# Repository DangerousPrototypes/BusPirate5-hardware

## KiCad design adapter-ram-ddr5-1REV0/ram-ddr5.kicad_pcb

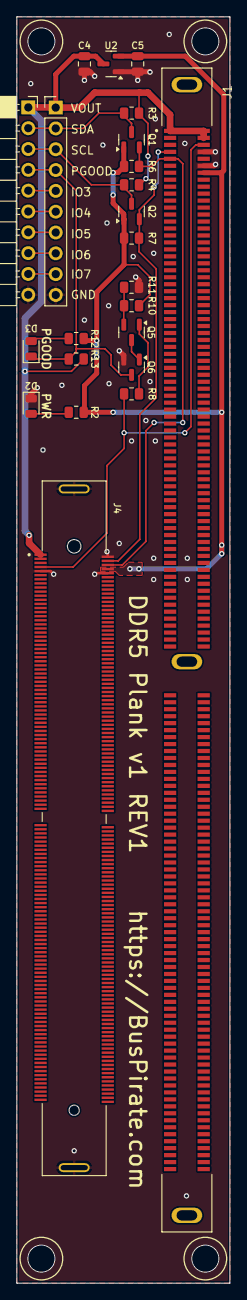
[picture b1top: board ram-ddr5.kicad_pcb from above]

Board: 2 copper layers, 26.0 x 154.5 mm, 23 parts (0 on the bottom side), 19 nets.

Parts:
C4, C5: 10uF/6.3V; C_0805_2012Metric
D2, D3: LED; LED_0805_2012Metric
J1: DDR504111002KQ; DDR5 UDIMM GENERIC
J2: Conn_01x10; PinSocket_1x10_P2.54mm_Horizontal
J3: Conn_01x10; PinHeader_1x10_P2.54mm_Vertical
J4: 10160554-001SHLF; AMPHENOL_10160554-001SHLF
Q1, Q2: 2N7002; SOT-23
Q5: BC807; SOT-23
Q6: BC817; SOT-23
R2, R12, R13: 6.8K; R_0805_2012Metric
R3, R4, R6, R7: 2K; R_0805_2012Metric
R8: 1K; R_0805_2012Metric
R10: 680R; R_0805_2012Metric
R11: 330R; R_0805_2012Metric
U2: MCP1700x-330xxTT; SOT-23

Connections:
+3.3V: C5.1, J1.151, J4.8, Q1.1 (G), Q2.1 (G), R2.1, R6.2, R7.2, R10.2, R12.1, U2.2 (VO)
BULK_VIN: C4.1, J1.01, J1.145, J1.146, J2.1, J3.1, J4.1, J4.3, R3.2, R4.2, R13.2, U2.3 (VI)
GND: C4.2, C5.2, D2.1 (K), J1.148, J1.150, J2.10, J3.10, J4.2, J4.9, J4.10, J4.SH, Q6.2 (E), R11.1, U2.1 (GND)
HSCL: J1.04, J4.4, Q2.2 (S), R7.1
HSDA: J1.05, J4.6, Q1.2 (S), R6.1
unnamed: D2.2 (A), R2.2
unnamed: D3.2 (A), R12.2
unnamed: J2.5, J3.5
unnamed: J2.6, J3.6
unnamed: J2.7, J3.7
unnamed: J2.8, J3.8
unnamed: J2.9, J3.9
unnamed: Q5.1 (B), R8.2
unnamed: Q5.3 (C), Q6.1 (B)
unnamed: Q5.2 (E), R10.1, R11.2
PWR_GOOD: J1.147, J4.7, R8.1
PWR_GOOD_OUT: D3.1 (K), J2.4, J3.4, Q6.3 (C), R13.1
SCL: J2.3, J3.3, Q2.3 (D), R4.1
SDA: J2.2, J3.2, Q1.3 (D), R3.1

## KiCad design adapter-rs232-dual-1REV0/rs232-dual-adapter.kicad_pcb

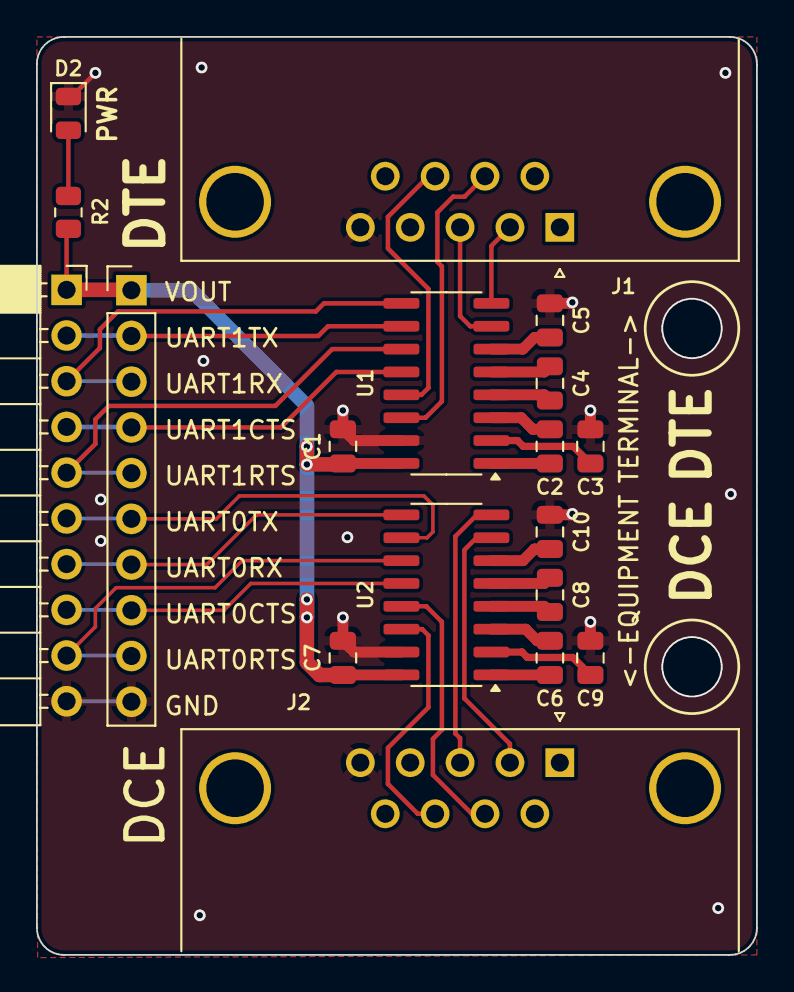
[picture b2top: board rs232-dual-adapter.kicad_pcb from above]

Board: 2 copper layers, 40.0 x 51.0 mm, 18 parts (0 on the bottom side), 31 nets.

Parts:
C1, C2, C6, C7: 0.1uF; C_0805_2012Metric
C3, C4, C5, C8, C9, C10: 0.47uF; C_0805_2012Metric
D2: LED; LED_0805_2012Metric
J1: COM1; DSUB-9_Male_Horizontal_P2.77x2.84mm_EdgePinOffset7.70mm_Hou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
J2: COM2; DSUB-9_Female_Horizontal_P2.77x2.84mm_EdgePinOffset7.70mm_H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
J3: Conn_01x10; PinHeader_1x10_P2.54mm_Vertical
J4: Conn_01x10; PinSocket_1x10_P2.54mm_Horizontal
R2: 2K; R_0805_2012Metric
U1, U2: MAX3232; SOP-16_3.9x9.9mm_P1.27mm

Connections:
/DCE_CTS: J2.8, U2.14 (T1OUT)
/DCE_RTS: J2.7, U2.13 (R1IN)
/DCE_RXD: J2.2, U2.7 (T2OUT)
/DCE_TXD: J2.3, U2.8 (R2IN)
/DTE_CTS: J1.8, U1.13 (R1IN)
/DTE_RTS: J1.7, U1.14 (T1OUT)
/DTE_RXD: J1.2, U1.8 (R2IN)
/DTE_TXD: J1.3, U1.7 (T2OUT)
GND: C1.2, C3.2, C5.2, C7.2, C9.2, C10.2, D2.1 (K), J1.5, J2.5, J3.10, J4.10, U1.15 (GND), U2.15 (GND)
unnamed: D2.2 (A), R2.2
unnamed: C2.1, U1.1 (C1+)
unnamed: C2.2, U1.3 (C1-)
unnamed: C4.1, U1.4 (C2+)
unnamed: C4.2, U1.5 (C2-)
unnamed: C3.1, U1.2 (VS+)
unnamed: C5.1, U1.6 (VS-)
unnamed: C6.1, U2.1 (C1+)
unnamed: C6.2, U2.3 (C1-)
unnamed: C8.1, U2.4 (C2+)
unnamed: C8.2, U2.5 (C2-)
unnamed: C9.1, U2.2 (VS+)
unnamed: C10.1, U2.6 (VS-)
UART0CTS: J3.8, J4.8, U2.12 (R1OUT)
UART0RTS: J3.9, J4.9, U2.11 (T1IN)
UART0RX: J3.7, J4.7, U2.9 (R2OUT)
UART0TX: J3.6, J4.6, U2.10 (T2IN)
UART1CTS: J3.4, J4.4, U1.12 (R1OUT)
UART1RTS: J3.5, J4.5, U1.11 (T1IN)
UART1RX: J3.3, J4.3, U1.9 (R2OUT)
UART1TX: J3.2, J4.2, U1.10 (T2IN)
VOUT: C1.1, C7.1, J3.1, J4.1, R2.1, U1.16 (VCC), U2.16 (VCC)

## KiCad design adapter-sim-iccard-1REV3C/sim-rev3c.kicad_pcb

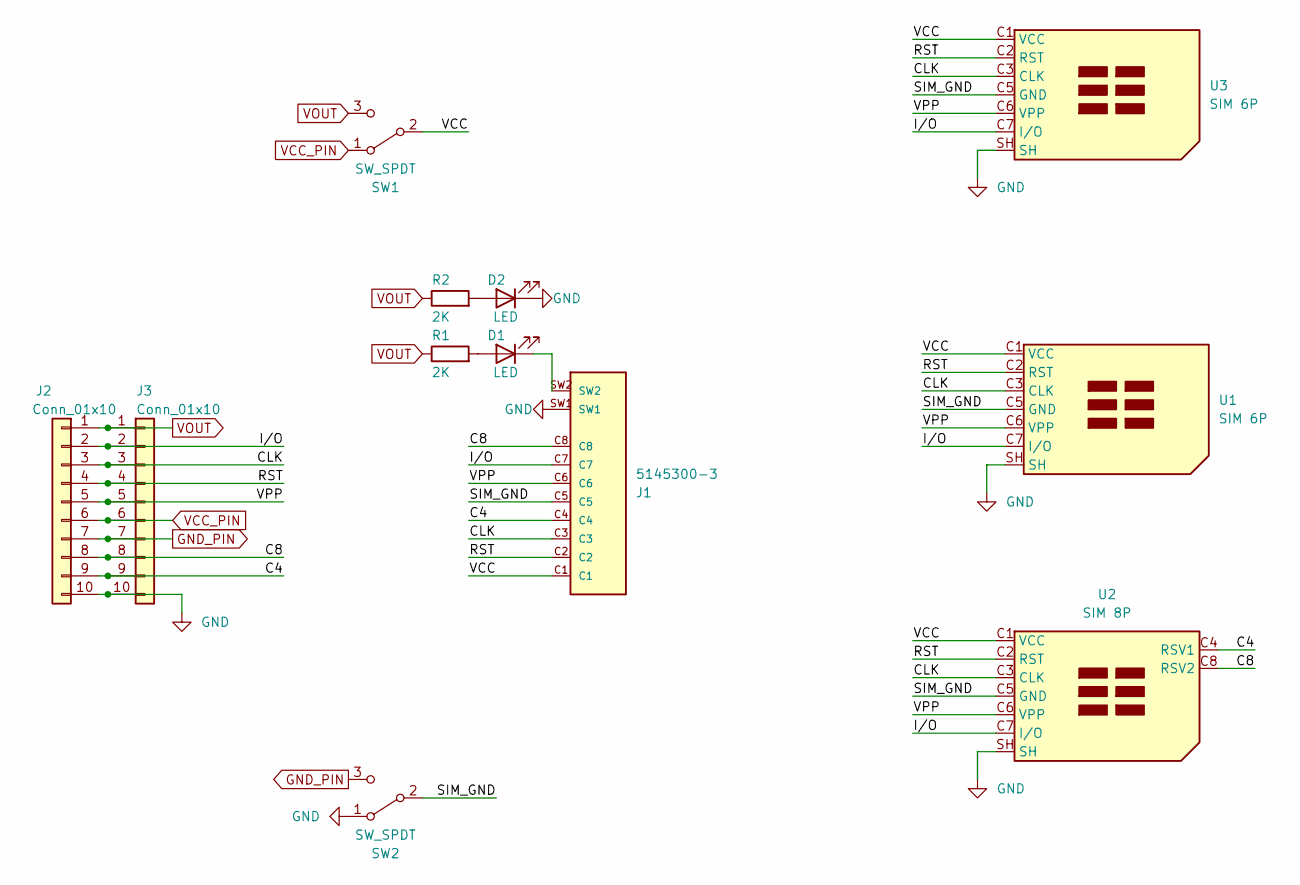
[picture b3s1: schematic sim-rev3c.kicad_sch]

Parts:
D1, D2: LED; LED_0805_2012Metric
J1: 5145300-3; TE_5145300-3; PARTREV C3
J2: Conn_01x10; PinSocket_1x10_P2.54mm_Horizontal
J3: Conn_01x10; PinHeader_1x10_P2.54mm_Vertical
R1, R2: 2K; R_0805_2012Metric
SW1, SW2: SW_SPDT; SW_SPDT_PCM12
U1: SIM 6P; DGLZ-SIM-0004
U2: SIM 8P; SIM-0030
U3: SIM 6P; SIM-0036

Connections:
/C4: J1.C4, J2.9, J3.9, U2.C4 (RSV1)
/C8: J1.C8, J2.8, J3.8, U2.C8 (RSV2)
/CLK: J1.C3, J2.3, J3.3, U1.C3 (CLK), U2.C3 (CLK), U3.C3 (CLK)
/I/O: J1.C7, J2.2, J3.2, U1.C7 (I/O), U2.C7 (I/O), U3.C7 (I/O)
/RST: J1.C2, J2.4, J3.4, U1.C2 (RST), U2.C2 (RST), U3.C2 (RST)
/SIM_GND: J1.C5, SW2.2 (B), U1.C5 (GND), U2.C5 (GND), U3.C5 (GND)
/VCC: J1.C1, SW1.2 (B), U1.C1 (VCC), U2.C1 (VCC), U3.C1 (VCC)
/VPP: J1.C6, J2.5, J3.5, U1.C6 (VPP), U2.C6 (VPP), U3.C6 (VPP)
GND: D2.1 (K), J1.SW1, J2.10, J3.10, SW2.1 (A), U1.SH, U2.SH, U3.SH
GND_PIN: J2.7, J3.7, SW2.3 (C)
unnamed: D1.2 (A), R1.2
unnamed: D1.1 (K), J1.SW2
unnamed: D2.2 (A), R2.2
VCC_PIN: J2.6, J3.6, SW1.1 (A)
VOUT: J2.1, J3.1, R1.1, R2.1, SW1.3 (C)

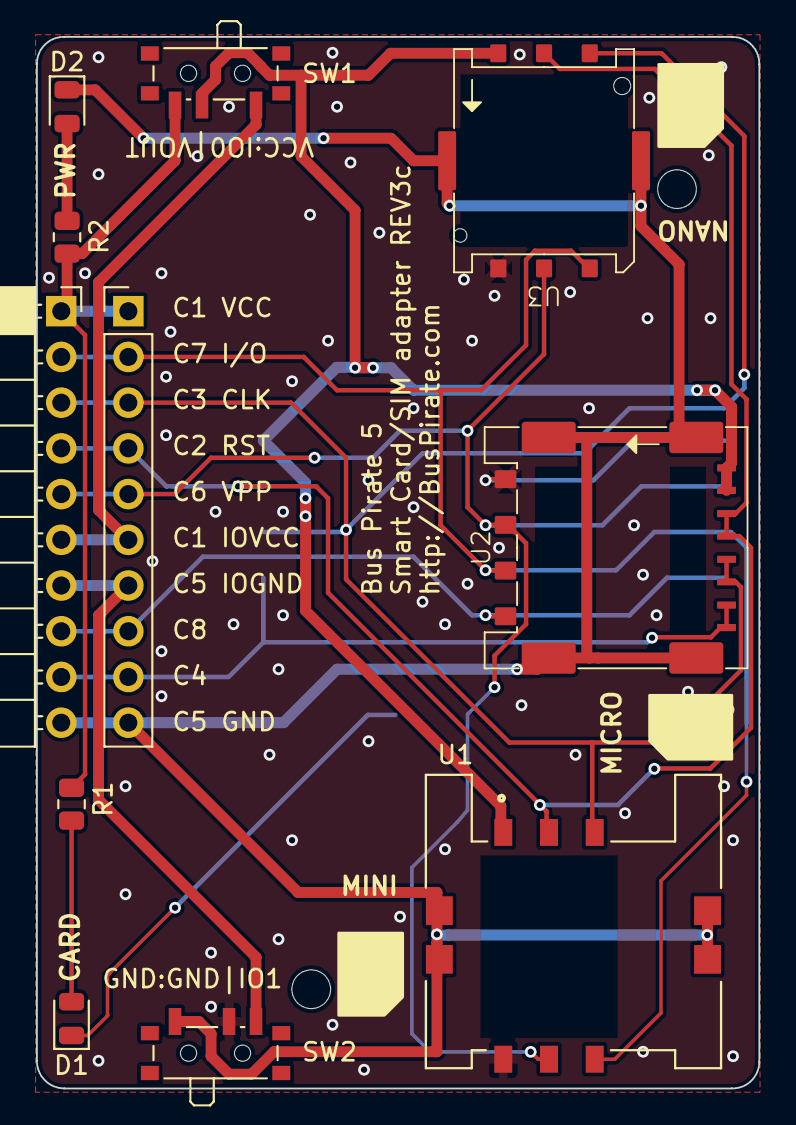
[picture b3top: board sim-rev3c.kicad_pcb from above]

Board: 2 copper layers, 40.1 x 58.4 mm, 12 parts (1 on the bottom side), 15 nets.

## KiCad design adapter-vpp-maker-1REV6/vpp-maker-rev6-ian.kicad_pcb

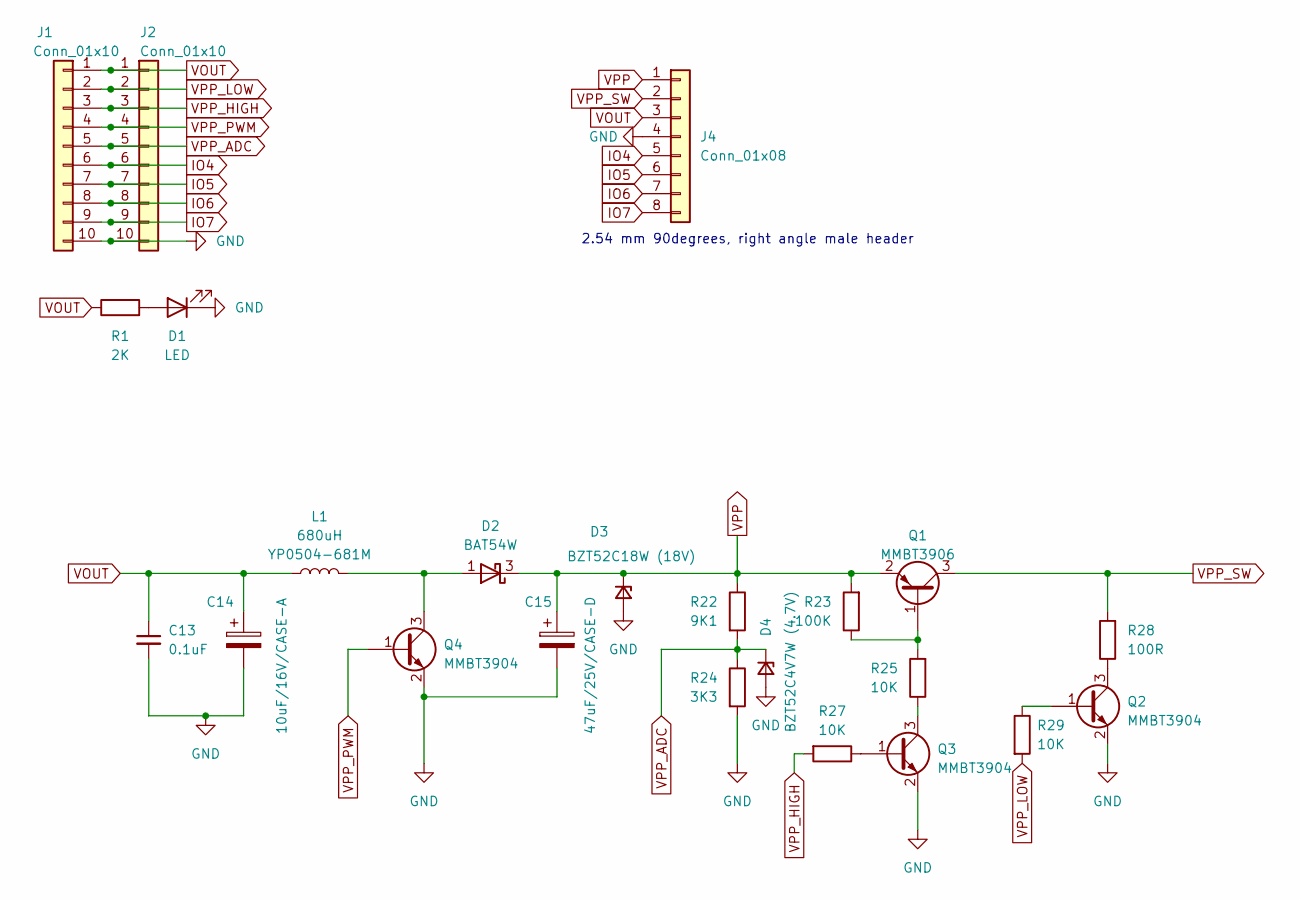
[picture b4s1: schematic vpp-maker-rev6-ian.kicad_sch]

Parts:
C13: 0.1uF; C_0805_2012Metric_Pad1.18x1.45mm_HandSolder
C14: 10uF/16V/CASE-A; CP_EIA-3216-18_Kemet-A
C15: 47uF/25V/CASE-D; CP_EIA-7343-31_Kemet-D
D1: LED; LED_0805_2012Metric
D2: BAT54W; SOT-23
D3: BZT52C18W (18V); D_SOD-123
D4: BZT52C4V7W (4.7V); D_SOD-123
J1: Conn_01x10; PinSocket_1x10_P2.54mm_Horizontal
J2: Conn_01x10; PinHeader_1x10_P2.54mm_Vertical
J4: Conn_01x08; PinHeader_1x08_P2.54mm_Horizontal
L1: 680uH; L_YP0504; MPN YP0504-681M
Q1: MMBT3906; SOT-23
Q2, Q3, Q4: MMBT3904; SOT-23
R1: 2K; R_0805_2012Metric
R22: 9K1; R_0805_2012Metric
R23: 100K; R_0805_2012Metric
R24: 3K3; R_0805_2012Metric
R25, R27, R29: 10K; R_0805_2012Metric
R28: 100R; R_0805_2012Metric

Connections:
GND: C13.2, C14.2, C15.2, D1.1 (K), D3.2 (A), D4.2 (A), J1.10, J2.10, J4.4, Q2.2 (E), Q3.2 (E), Q4.2 (E), R24.2
IO4: J1.6, J2.6, J4.5
IO5: J1.7, J2.7, J4.6
IO6: J1.8, J2.8, J4.7
IO7: J1.9, J2.9, J4.8
unnamed: D1.2 (A), R1.2
unnamed: D2.1 (A), L1.2, Q4.3 (C)
unnamed: Q1.1 (B), R23.1, R25.2
unnamed: Q2.1 (B), R29.1
unnamed: Q2.3 (C), R28.1
unnamed: Q3.1 (B), R27.1
unnamed: Q3.3 (C), R25.1
VOUT: C13.1, C14.1, J1.1, J2.1, J4.3, L1.1, R1.1
VPP: C15.1, D2.3 (K), D3.1 (K), J4.1, Q1.2 (E), R22.1, R23.2
VPP_ADC: D4.1 (K), J1.5, J2.5, R22.2, R24.1
VPP_HIGH: J1.3, J2.3, R27.2
VPP_LOW: J1.2, J2.2, R29.2
VPP_PWM: J1.4, J2.4, Q4.1 (B)
VPP_SW: J4.2, Q1.3 (C), R28.2

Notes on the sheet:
2.54 mm 90degrees, right angle male header

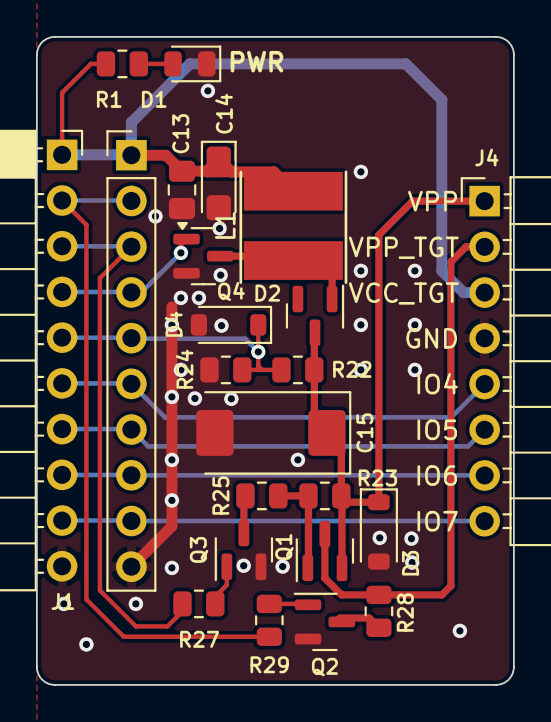
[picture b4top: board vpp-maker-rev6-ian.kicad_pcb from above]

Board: 2 copper layers, 26.5 x 36.0 mm, 23 parts (0 on the bottom side), 19 nets.

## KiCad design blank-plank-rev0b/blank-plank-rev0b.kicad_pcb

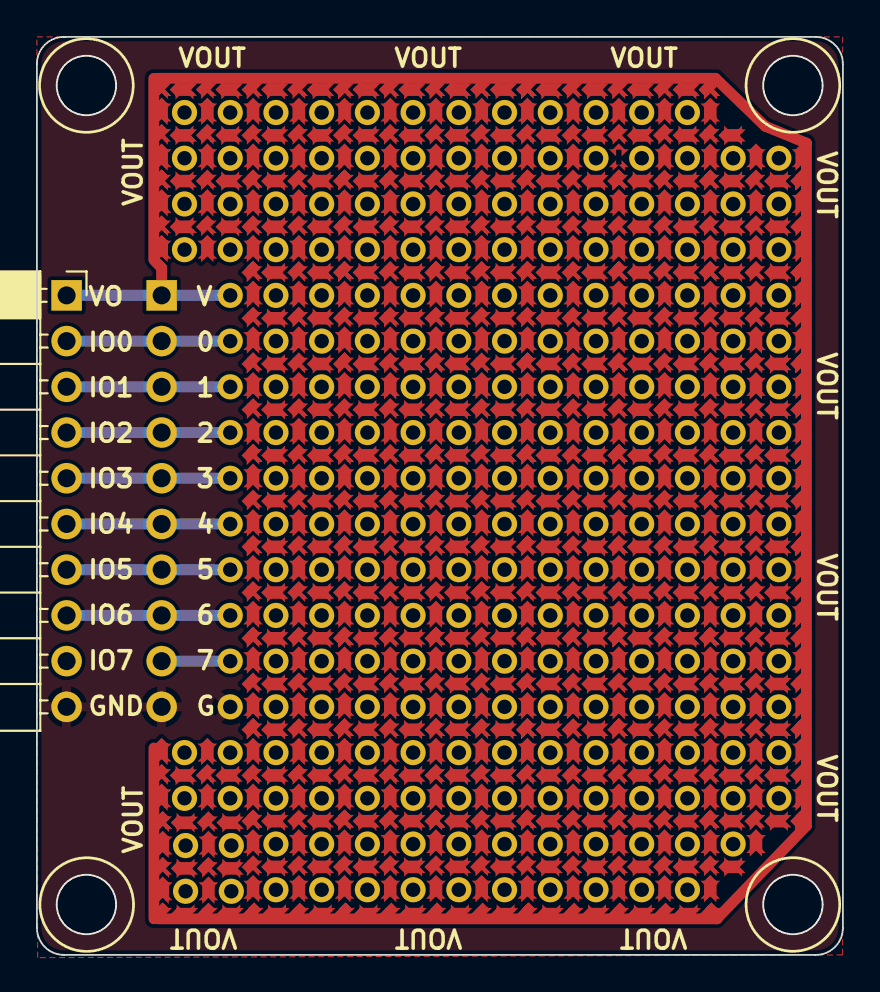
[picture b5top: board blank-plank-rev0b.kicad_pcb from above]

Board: 2 copper layers, 44.8 x 51.0 mm, 3 parts (0 on the bottom side), 10 nets.

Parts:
J2: Conn_01x10; PinSocket_1x10_P2.54mm_Horizontal
J3: Conn_01x10; PinHeader_1x10_P2.54mm_Vertical_No_Silk
J5: Conn_01x10; PinHeader_1x10_P2.54mm_Vertical_Reduced_2

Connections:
GND: J2.10, J3.10, J5.10
IO0: J2.2, J3.2, J5.2
IO1: J2.3, J3.3, J5.3
IO2: J2.4, J3.4, J5.4
IO3: J2.5, J3.5, J5.5
IO4: J2.6, J3.6, J5.6
IO5: J2.7, J3.7, J5.7
IO6: J2.8, J3.8, J5.8
IO7: J2.9, J3.9, J5.9
VOUT: J2.1, J3.1, J5.1

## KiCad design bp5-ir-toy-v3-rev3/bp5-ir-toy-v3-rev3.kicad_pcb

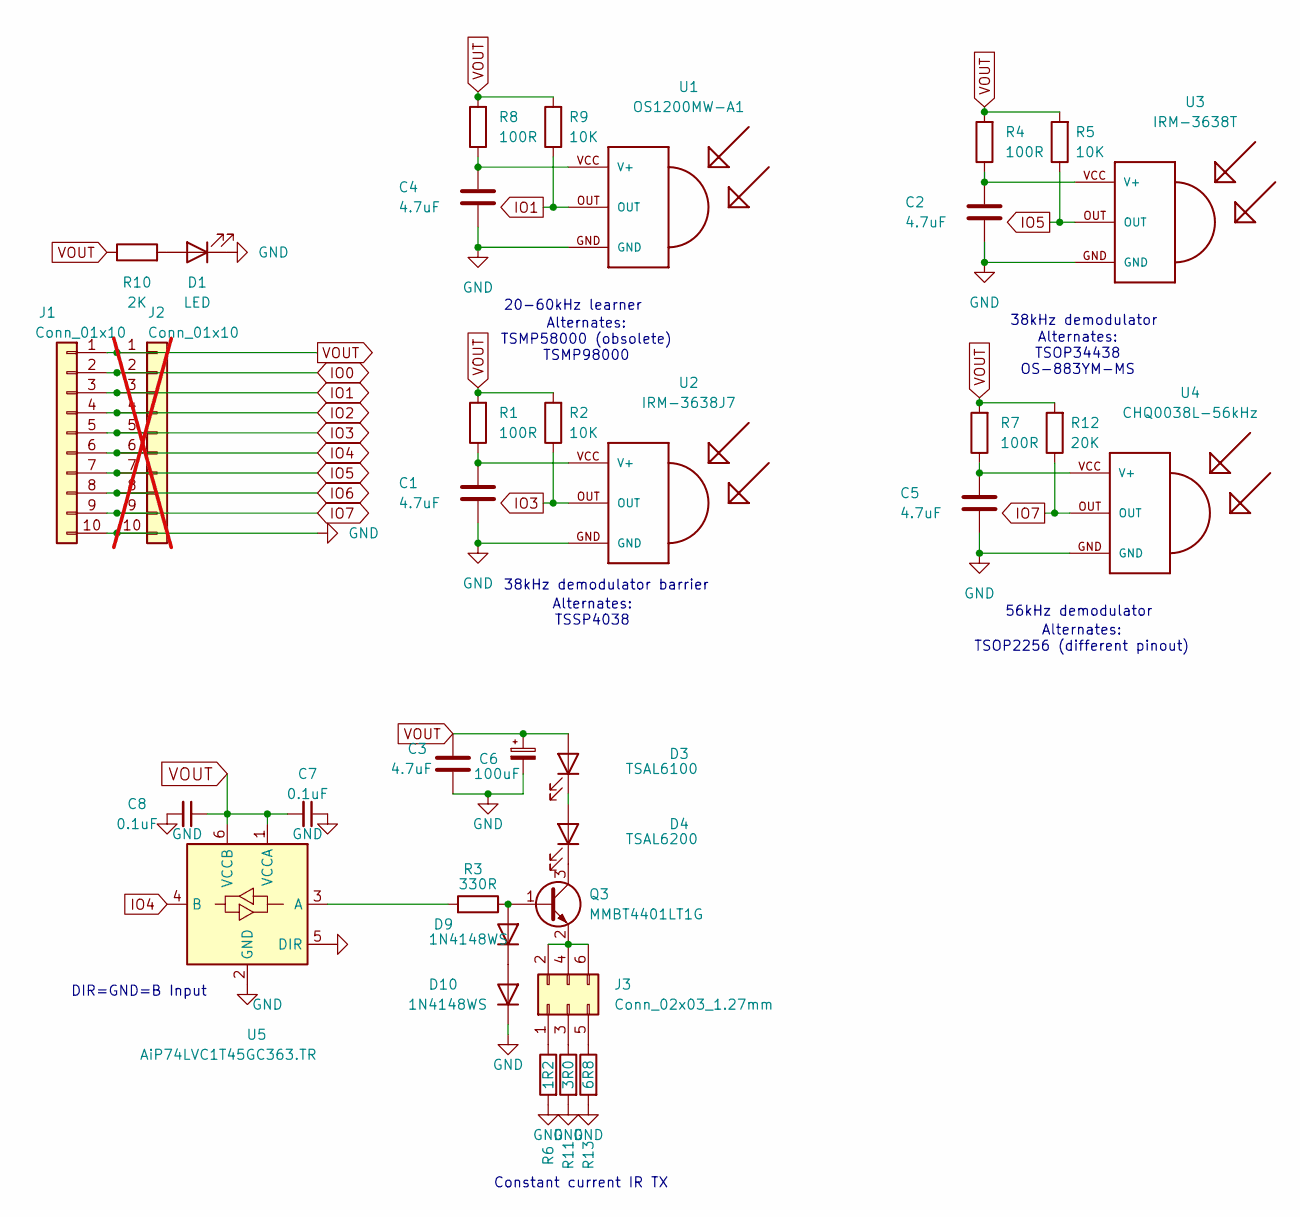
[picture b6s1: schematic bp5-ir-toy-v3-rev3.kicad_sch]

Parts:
C1, C2, C3, C4, C5: 4.7uF; C_0805_2012Metric
C6: 100uF; CP_EIA-3528-21_Kemet-B_Pad1.50x2.35mm_HandSolder
C7, C8: 0.1uF; C_0805_2012Metric
D1: LED; LED_0805_2012Metric
D3: TSAL6100; LED_D5.0mm_Horizontal_O1.27mm_Z3.0mm_IRGrey
D4: TSAL6200; LED_D5.0mm_Horizontal_O1.27mm_Z3.0mm_IRGrey
D9, D10: 1N4148WS; D_SOD-323F
J1: Conn_01x10; PinSocket_1x10_P2.54mm_Horizontal
J2: Conn_01x10; PinHeader_1x10_P2.54mm_Vertical; not fitted
J3: Conn_02x03_1.27mm; PinHeader_2x03_P1.27mm_Vertical
Q3: MMBT4401LT1G; SOT-23
R1, R4, R7, R8: 100R; R_0805_2012Metric
R2, R5, R9: 10K; R_0805_2012Metric
R3: 330R; R_0805_2012Metric
R6: 1R2; R_1206_3216Metric
R10: 2K; R_0805_2012Metric
R11: 3R0; R_1206_3216Metric
R12: 20K; R_0805_2012Metric
R13: 6R8; R_1206_3216Metric
U1: OS1200MW-A1; TSOP18XX
U2: IRM-3638J7; TSOP18XX
U3: IRM-3638T; TSOP18XX
U4: CHQ0038L-56kHz; TSOP18XX
U5: AiP74LVC1T45GC363.TR; SOT-363_SC-70-6

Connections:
GND: C1.2, C2.2, C3.2, C4.2, C5.2, C6.2, C7.1, C8.2, D1.1 (K), D10.1 (K), J1.10, J2.10, R6.2, R11.2, R13.2, U1.GND, U2.GND, U3.GND, U4.GND, U5.2 (GND), U5.5 (DIR)
IO0: J1.2, J2.2
IO1: J1.3, J2.3, R9.1, U1.OUT
IO2: J1.4, J2.4
IO3: J1.5, J2.5, R2.1, U2.OUT
IO4: J1.6, J2.6, U5.4 (B)
IO5: J1.7, J2.7, R5.1, U3.OUT
IO6: J1.8, J2.8
IO7: J1.9, J2.9, R12.1, U4.OUT
unnamed: D1.2 (A), R10.2
unnamed: D3.1 (K), D4.2 (A)
unnamed: D4.1 (K), Q3.3 (C)
unnamed: D9.2 (A), Q3.1 (B), R3.1
unnamed: D9.1 (K), D10.2 (A)
unnamed: J3.1, R6.1
unnamed: J3.2, J3.4, J3.6, Q3.2 (E)
unnamed: J3.3, R11.1
unnamed: J3.5, R13.1
unnamed: C4.1, R8.1, U1.VCC (V+)
unnamed: C1.1, R1.1, U2.VCC (V+)
unnamed: C2.1, R4.1, U3.VCC (V+)
unnamed: C5.1, R7.1, U4.VCC (V+)
unnamed: R3.2, U5.3 (A)
VOUT: C3.1, C6.1, C7.2, C8.1, D3.2 (A), J1.1, J2.1, R1.2, R2.2, R4.2, R5.2, R7.2, R8.2, R9.2, R10.1, R12.2, U5.1 (VCCA), U5.6 (VCCB)

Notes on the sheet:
Constant current IR TX
38kHz demodulator
56kHz demodulator
Alternates: TSMP58000 (obsolete) TSMP98000
38kHz demodulator barrier
Alternates: TSOP2256 (different pinout)
Alternates: TSOP34438 OS-883YM-MS
Alternates: TSSP4038
20-60kHz learner
DIR=GND=B Input

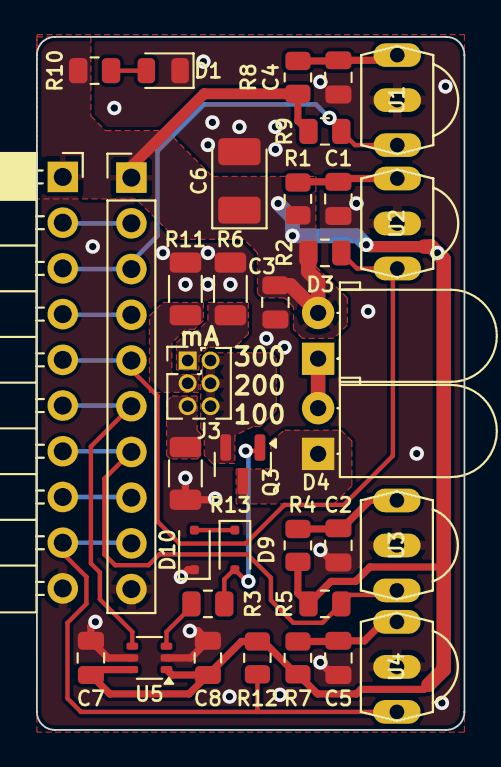
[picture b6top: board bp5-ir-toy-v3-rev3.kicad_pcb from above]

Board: 2 copper layers, 23.8 x 38.5 mm, 35 parts (0 on the bottom side), 24 nets.

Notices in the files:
blank-plank-rev0b/blank-plank-rev0b.kicad_pcb:
Proto-Pattern CC-BY 4.0
